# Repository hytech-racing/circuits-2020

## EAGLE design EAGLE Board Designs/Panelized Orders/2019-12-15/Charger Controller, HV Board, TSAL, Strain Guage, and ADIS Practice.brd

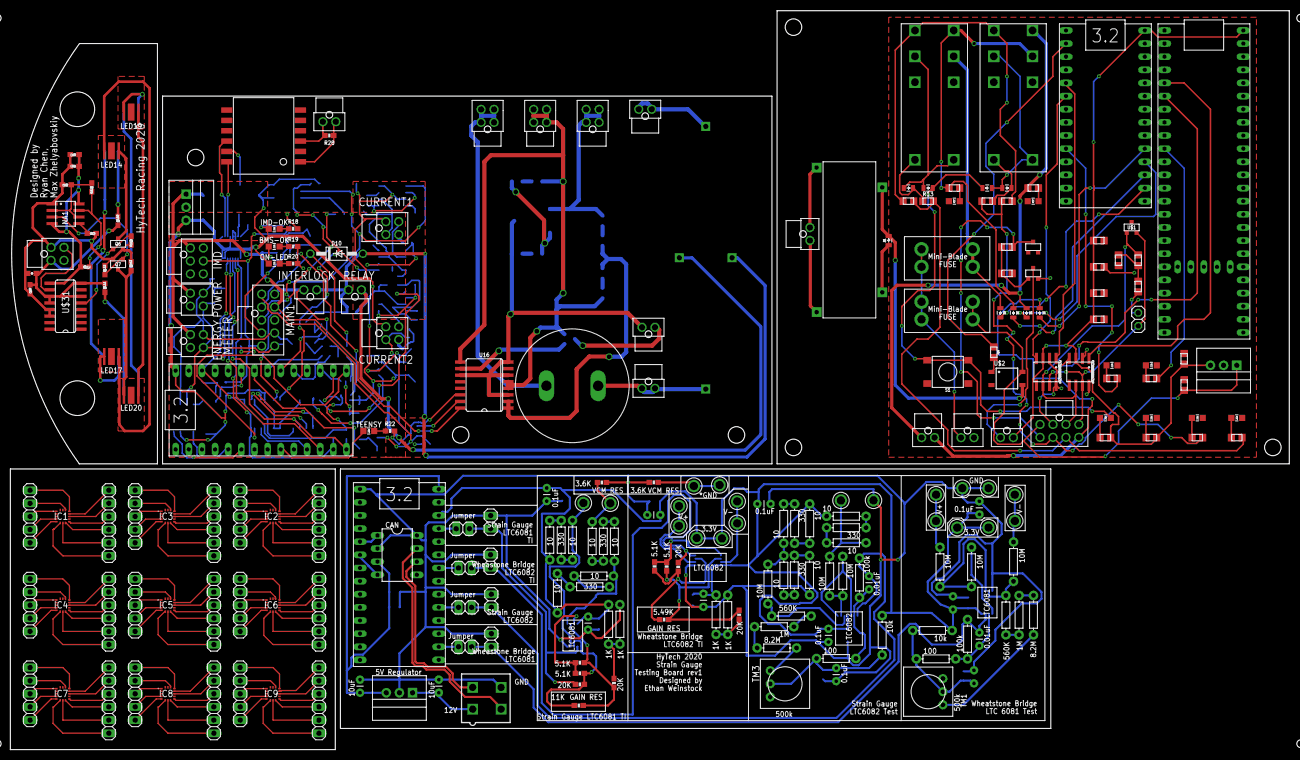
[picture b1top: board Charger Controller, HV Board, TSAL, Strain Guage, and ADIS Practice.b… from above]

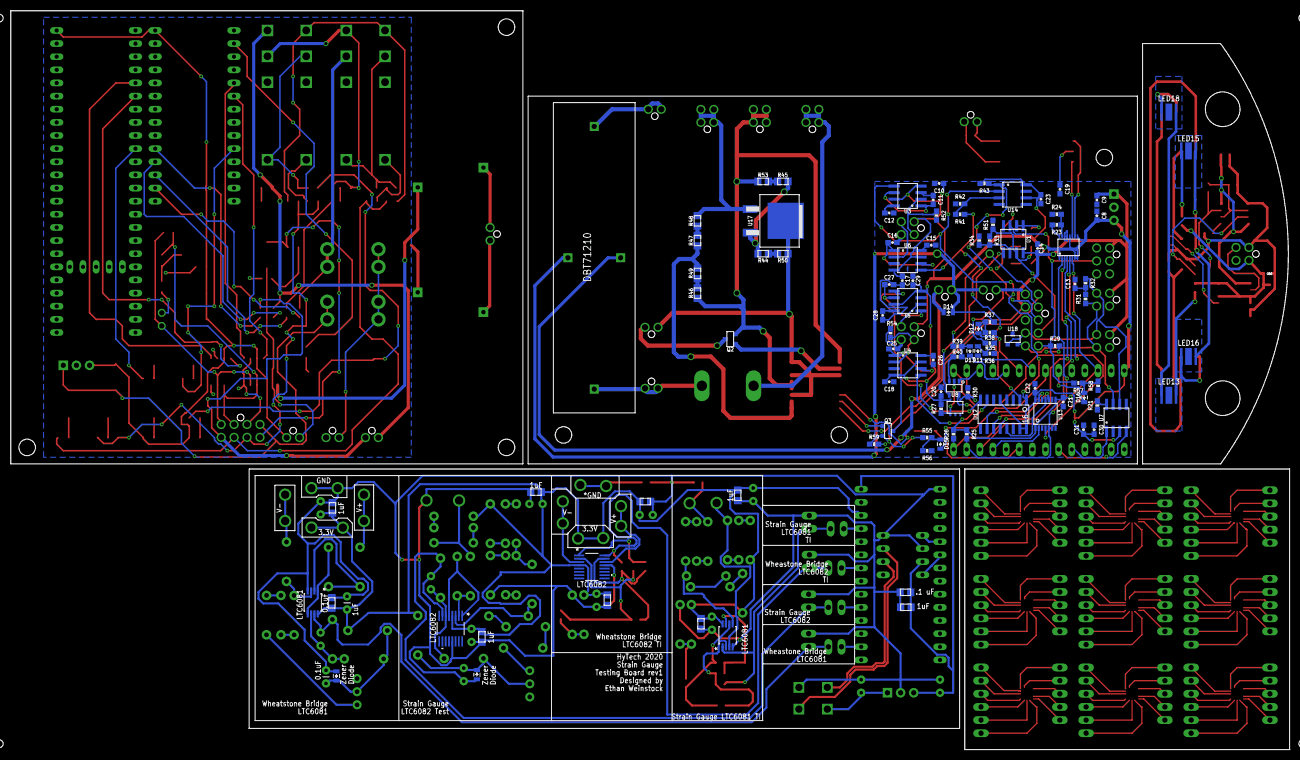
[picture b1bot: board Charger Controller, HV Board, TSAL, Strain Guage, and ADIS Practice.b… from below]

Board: 2 copper layers, 247.3 x 142.9 mm, 344 parts (105 on the bottom side), 312 nets.

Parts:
5ABOARDFUSE, 5ASHUTDOWNFUSE: MINI-BLADE_FUSE_HOLDER
BMS-OK: GREEN; LED-805
BMS_SHUTDOWN_RLY: RT424009; RELAY_DPDT
C1, C6, C40, C43, C47, C49, C55, C57, C59, C60: 1uF; 0805
C2, C7: .1uF; 0805
C3, C4: 10uF; 0805
C5: 4.7nF; 0805
C8, C9: 10uF; 0603-CAP
C10, C11, C14, C16, C17, C18, C20, C21, C22, C23, C25, C27, C29, C30, C31, C64, C67: 0.1uF; 0603-CAP
C12, C15, C26, C28: 530pF; 0603-CAP
C13: 4.7nF; 0603-CAP
C19: 27pF; 0603-CAP
C24: 180µF; LLS2V221MELZ
C38: 0.1uF; 0805
C39, C42, C44, C46, C48, C50, C56, C58, C61: 0.1uF; CAP-PTH-SMALL
C41, C45: 0.01uF; CAP-PTH-SMALL
C51: 1uF; CAP-PTH-SMALL
C52, C53: 10uF; CAP-PTH-SMALL
C54: .1 uF; 0805
C62: 4.7uF; 0603-CAP
C63: 10nF; 0603-CAP
C65, C66: 1uF; 0603-CAP
CAN_TERM_JMP: M02_SLIM; 1X02_SLIM
CAN_TRANSCEIVER_3.2, CAN_TRANSCEIVER_3.5: MCP2551; SOIC-08
CHARGER: CHARGE CONTROL; NANO-FIT_VERTICAL-2
CURRENT1, CURRENT2: CURRENT; NANO-FIT_VERTICAL-4
D1, D2, D4, D5, D6, D7, D8, D9, D11, D12, D13, D14, D15, D16: TS4148 RYG; 0805_D
D3: DIODE; 0805_D
D10: DIODE; DO-41
DISCH+: DISCHARGE+; NANO-FIT_VERTICAL-2
ENERGYMETER: ENERGY METER; NANO-FIT_VERTICAL-4
HV+FUSED_1A-IMD+: HV+; NANO-FIT_VERTICAL-4
HV+UNFUSED: HV+UNFUSED; NANO-FIT_VERTICAL-2
HV-FUSED_1A-IMD-: HV-; NANO-FIT_VERTICAL-4
HV-UNFUSED_DISCHARGE-: HV-UNFUSED; NANO-FIT_VERTICAL-4
IC1, IC2, IC3, IC4, IC5, IC6, IC7, IC8, IC9: KX124-1051; 3X3LGA
IMD: IMD; NANO-FIT_VERTICAL-6
IMD-OK: YELLOW; LED-805
IMD_SHUTDOWN_RLY: RT424009; RELAY_DPDT
INDICATOR: INDICATOR; NANO-FIT_VERTICAL-2
INTERLOCK: INTERLOCK; NANO-FIT_VERTICAL-2
ISO_SPI: ISO_SPI; NANO-FIT_VERTICAL-2
J1, J2, J3, J4: JUMPER.1; 1X02
JP1, JP2, JP5, JP7, JP9, JP11, JP13, JP15, JP17: 1X06
JP3, JP4, JP6, JP8, JP10, JP12, JP14, JP16, JP18: 1X05
JP19, JP20, JP21, JP22: M02; 1X02
LED1: Purple; LED-805
LED3: Yellow; LED-805
LED4: Green; LED-805
LED6: White; LED-805
LED13, LED18, LED19, LED20: RED; XP-E2
LED14, LED15, LED16, LED17: GRN; XP-E2
LT1790B, LT1790B2: 1.25V; 0805_D
MAIN: MAIN CONNECTOR; NANO-FIT_VERTICAL-8
MAIN1: MAIN; NANO-FIT_VERTICAL-10
NA1: NA555SO-8; SOIC-08
ON-LED: PURPLE; LED-805
POWER: POWER; NANO-FIT_VERTICAL-2
POWER1: POWER; NANO-FIT_VERTICAL-4
POWERTAIL: Powerswitch Tail; NANO-FIT_VERTICAL-2
Q1, Q6, Q7: SOT23
Q2, Q3: DMG3406L; SOT23
R1, R13: 20; 0805
R1_1, R1_3, R1_6, R1_8: 5.1K; 0603-RES
R1_2, R1_4, R1_5, R1_7: 20K; 0603-RES
R1_9: 5.49K; 0603-RES
R1_11: 11K; 0603-RES
R2, R3, R7, R16, R44, R50: 2k; 0805
R4, R45, R53: 20k; 0805
R5: 270; 0805
R6: 5.1k; 0805
R8: 33; 0805
R9, R10: 60; 0805
R11: 40k; 0805
R12: 10k; 0805
R14: 360; 0805
R15, R17: 68; 0805
R18: 820; 0603-RES
R19, R25, R26, R29, R34, R43, R51, R59, R113, R114, R115: 2k; 0603-RES
R20: 270; 0603-RES
R21, R23, R24, R112: 1k; 0603-RES
R22: 43; 0603-RES
R27: 430; 0603-RES
R28: 100; 0603-RES
R30: 10k; 0603-RES
R31, R32: 60; 0603-RES
R33: 4k; 0603-RES
R35, R37, R39, R57: 43k; 0603-RES
R36, R38, R40, R58: 12k; 0603-RES
R41: 261; 0603-RES
R42: 5K; 0603-RES
R46: 1.4k; 0805
R47, R48: 510k; 0805
R49: 14k; 0805
R52, R54: 10K; 0603-RES
R55, R56: 5k; 0603-RES
R67, R70, R71, R72, R74, R85: 10M; AXIAL-0.3
R68, R69, R78, R80, R82, R83, R87, R89, R99, R100, R102, R103: 10; AXIAL-0.3
R73, R81: 8.2M; AXIAL-0.3
R75, R91: 100k; AXIAL-0.3
R76, R95: 100; AXIAL-0.3
R77, R96: 10k; AXIAL-0.3
R79, R84, R86, R88, R98, R104: 330; AXIAL-0.3
R90, R93: 1M; AXIAL-0.3
R92, R94: 560K; AXIAL-0.3
R97, R108: 3.6K; 0603-RES
R101, R105, R106, R107: 1K; AXIAL-0.3
R109, R111: 330R; 0603-RES
R110: 50k; 0603-RES
REG, REG1: 5V; OKI-78SR
RELAY: RELAY; NANO-FIT_VERTICAL-2
S1: TACTILE_SWITCH_SMD_6.2MM_TALL
SHUTDOWN_B: Yellow; LED-805
SHUTDOWN_BUTTON: Shutdown Button; NANO-FIT_VERTICAL-2
SHUTDOWN_C: Green; LED-805
STATUS, STATUS1: RED; LED-805
TEENSY: BLUE; LED-805
TEENSY3.2: TEENSY_3.2_SIMPLE
TM1, TM3: 500k; TRIM-3386
U1: OPA2172; SOIC-08
U2: OKI-78SR-5; OKI-78SR
U3, U4, U5, U6: MAX7480; SOIC-08
U7: MCP2551; SOIC-08
U8: SN74LVC1G08; SOT-23-5
U9: LTC6820; MSOP-16
U10: STWD100; SOT23-5
U11: HM2102NLT
U12: MCP3208SOIC; SOIC-16
U13: TXB0104TSSOP; TSSOP-14
U14: MCP6542SOIC; SOIC-08
U15: DBT71210
U16: UCC21520A; SO16-DW
U17: LR8; TO-252
U18: CDSOT23-T24CAN-Q; SOT23
U19, U20: LTC6082CGNPBF; SSOP-16_GN
U$1: CDSOT23-T24CAN-Q; SOT23
U$2: CPC1002N; SOP04
U$3: KT12-1A-40L-THT
U$4, U$8: TEENSY_3.2_SIMPLE
U$5: TEENSY_3.5_EXT
U$7, U$21: LTC6081; MSOP-8_MS
U$9, U$10, U$11, U$12, U$13, U$14, U$15, U$16, U$17, U$18, U$19, U$20, U$23, U$24, U$25, U$26, U$27, U$28, U$29, U$30: TEST_POINT
U$22: MCP2551DIL; DIL08
U$31: MAX4622; SO16
X2: CONNECTOR-4; MINIFIT_5566-4
X3: CONNECTOR-4NANO-FIT-VERTICAL-4; NANO-FIT_VERTICAL-4
ZENER: SOT23

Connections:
3V3: C38.2, C39.1, C40.1, C42.2, C43.1, C46.1, C47.1, C48.1, C49.1, C51.1, C56.2, C57.1, C58.1, C59.1, C60.1, C61.2, R77.P$2, R78.P$1, R80.P$1, R96.P$2, R99.P$2, R101.P$2, R103.P$2, R106.P$2, U19.4, U20.4, U$7.8, U$8.3.3V, U$11.P$1, U$18.P$1, U$21.8, U$23.P$1, U$30.P$1
60V_THRESHOLD_SIGNAL: MAIN1.P$1, Q3.2, R55.1, R59.1
60V_THRESHOLD_TEENSY: D15.C, TEENSY3.2.A6
+3V3: C21.1, R25.1, R26.1, TEENSY3.2.3.3V, U8.5, U9.6, U13.1, U13.8
+5V: C1.2, C2.2, C4.2, C6.2, C7.2, CAN_TRANSCEIVER_3.2.3, CAN_TRANSCEIVER_3.5.3, POWERTAIL.P$1, R5.1, R6.1, REG.3, U$4.VIN, U$5.VIN
+5V1: C8.1, C10.1, C17.1, C18.1, C20.1, C22.1, C23.1, C29.1, C30.1, C31.1, CURRENT1.P$1, CURRENT2.P$1, ON-LED.A, Q3.3, R27.1, R43.2, TEENSY3.2.VIN, U2.3, U3.4, U3.7, U4.4, U4.7, U5.4, U5.7, U6.4, U6.7, U7.3, U9.1, U9.7, U9.8, U9.9, U9.12, U10.VCC, U12.5, U12.15, U12.16, U13.14, U14.6, U14.8
+5V2: C53.2, C54.2, C55.2, REG1.3, U$8.VIN, U$22.3
+12V: 5ABOARDFUSE.R1, 5ABOARDFUSE.R2, C3.2, MAIN.P$4, REG.1, U$2.4
+12V1: C9.1, C14.1, ENERGYMETER.P$1, IMD.P$1, MAIN1.P$7, POWER1.P$1, U1.8, U2.1, U16.16
+12V2: C52.2, REG1.1, X2.1
+12VIN: 5ABOARDFUSE.L1, 5ABOARDFUSE.L2, 5ASHUTDOWNFUSE.L1, 5ASHUTDOWNFUSE.L2, POWER.P$2
BMS_OK: MAIN.P$7, R1.1, R2.1, R8.1
BMS_OK_3.3V: U1.5, U8.4
BMS_OK_10V: BMS-OK.A, MAIN1.P$4, R33.2, R51.1, U1.7
BMS_OK_RELAY: BMS_SHUTDOWN_RLY.COIL+, D6.C, R1.2
BMS_PWR_STEP: BMS_SHUTDOWN_RLY.3, BMS_SHUTDOWN_RLY.COIL-, D1.A, D6.A
BSPD_CURR_REFERENCE: R41.1, R42.2, U14.3
BSPD_CURR_SIGNAL: MAIN1.P$3, R43.1, U14.1
CANH: CAN_TERM_JMP.1, CAN_TRANSCEIVER_3.2.7, CAN_TRANSCEIVER_3.5.7, MAIN.P$1, U$1.2
CANH1: ENERGYMETER.P$4, MAIN1.P$10, POWER1.P$4, R31.2, U7.7, U18.2
CANH2: U$22.7, X2.3
CANL: CAN_TRANSCEIVER_3.2.6, CAN_TRANSCEIVER_3.5.6, MAIN.P$2, R9.1, U$1.1
CANL1: ENERGYMETER.P$3, MAIN1.P$9, POWER1.P$3, R32.2, U7.6, U18.1
CANL2: U$22.6, X2.2
CHARGER_1: CHARGER.P$1, U$3.S1
CHARGER_2: CHARGER.P$2, U$3.S2
CHARGE_CONTROL: D3.C, U$2.3, U$3.C1
CHARGE_ENABLE: MAIN.P$8, R11.2, ZENER.3
CHARGE_ENABLE1: D10.C, MAIN1.P$2, R39.1
CHARGE_ENABLE_TEENSY: D13.C, TEENSY3.2.A3
CS_LTC6820: TEENSY3.2.D10(TX2), U9.5
CS_MCP3208_3.3V: TEENSY3.2.D9(RX2), U13.2
CURR1_SENSE: CURRENT1.P$2, R52.1, U3.2
CURR1_SENSE_FILTERED: U3.5, U12.1, U14.2
CURR2_SENSE: CURRENT2.P$2, R54.1, U4.2
CURR2_SENSE_FILTERED: U4.5, U12.7
DISCHARGE_RELAY_GND: D14.A, RELAY.P$2, U15.COIL-
GND: C1.1, C2.1, C3.1, C4.1, C5.2, C6.1, C7.1, CAN_TRANSCEIVER_3.2.2, CAN_TRANSCEIVER_3.2.8, CAN_TRANSCEIVER_3.5.2, CAN_TRANSCEIVER_3.5.8, D3.A, LED1.C, LED3.C, LED4.C, MAIN.P$3, POWER.P$1, Q1.2, R12.1, REG.2, S1.B1, S1.B2, SHUTDOWN_B.C, SHUTDOWN_C.C, STATUS.C, STATUS1.C, U$1.3, U$2.2, U$3.C2, U$4.GND, U$5.GND, ZENER.1
GND1: C8.2, C9.2, C10.2, C11.2, C12.2, C13.1, C14.2, C15.2, C16.2, C17.2, C18.2, C19.2, C20.2, C21.2, C22.2, C23.2, C25.2, C26.2, C27.2, C28.2, C29.2, C30.2, C31.2, CURRENT1.P$4, CURRENT2.P$4, ENERGYMETER.P$2, IMD.P$2, IMD.P$3, IMD.P$4, MAIN1.P$8, POWER1.P$2, R18.1, R19.2, R20.2, R21.1, R22.2, R24.2, R29.2, R30.2, R34.1, R36.1, R38.1, R40.1, R42.1, R51.2, R52.2, R54.2, R56.1, R58.1, R59.2, TEENSY3.2.AGND, TEENSY3.2.GND, U1.4, U2.2, U3.3, U4.3, U5.3, U6.3, U7.2, U8.3, U9.13, U9.14, U10.EN, U10.GND, U12.4, U12.9, U12.14, U13.7, U14.4, U14.5, U16.14, U18.3
GND1_A: IC1.5, JP10.1
GND1_B: IC2.5, JP12.1
GND1_C: IC3.5, JP6.1
GND1_D: IC4.5, JP4.1
GND1_E: IC5.5, JP8.1
GND1_F: IC6.5, JP3.1
GND1_G: IC7.5, JP14.1
GND1_H: IC8.5, JP16.1
GND1_I: IC9.5, JP18.1
GND2_A: IC1.12, JP9.6
GND2_B: IC2.12, JP11.6
GND2_C: IC3.12, JP5.6
GND2_D: IC4.12, JP1.6
GND2_E: IC5.12, JP7.6
GND2_F: IC6.12, JP2.6
GND2_G: IC7.12, JP13.6
GND2_H: IC8.12, JP15.6
GND2_I: IC9.12, JP17.6
GND3: C38.1, C39.2, C40.2, C42.1, C43.2, C44.1, C46.2, C47.2, C48.2, C49.2, C50.1, C51.2, C52.1, C53.1, C54.1, C55.1, C56.1, C57.2, C58.2, C59.2, C60.2, C61.1, JP19.1, JP20.1, JP21.1, JP22.1, LT1790B.A, LT1790B2.A, R89.P$1, R97.1, R105.P$1, R107.P$1, R108.1, REG1.2, U19.13, U20.13, U$7.4, U$8.GND, U$14.P$1, U$15.P$1, U$20.P$1, U$21.4, U$22.2, U$22.8, X2.4
GND4: C62.2, C63.2, C64.2, C65.2, C66.2, C67.2, NA1.1, Q6.2, Q7.2, R113.2, R114.2, R115.2, U$31.13, U$31.14, X3.P$1
GRN1: Q6.1, R114.1, U$31.5
HV+FUSED_1A: HV+FUSED_1A-IMD+.P$1, HV+FUSED_1A-IMD+.P$2, HV+FUSED_1A-IMD+.P$3, HV+FUSED_1A-IMD+.P$4, R48.2, U17.1
HV+UNFUSED: C24.P$1, HV+UNFUSED.P$1, HV+UNFUSED.P$2, U15.CONTACT1
HV+UNFUSED_FSAE_DISCHARGE: DISCH+.P$1, DISCH+.P$2, U15.CONTACT2
HV-FUSED_1A: HV-FUSED_1A-IMD-.P$1, HV-FUSED_1A-IMD-.P$2, HV-FUSED_1A-IMD-.P$3, HV-FUSED_1A-IMD-.P$4, Q2.2, R46.1, R53.2, U16.4, U16.5, U16.9
HV-UNFUSED: C24.P$2, HV-UNFUSED_DISCHARGE-.P$1, HV-UNFUSED_DISCHARGE-.P$2, HV-UNFUSED_DISCHARGE-.P$3, HV-UNFUSED_DISCHARGE-.P$4
IM: U9.10, U11.P$10
IMD_PWR_STEP: D7.A, D9.A, IMD_SHUTDOWN_RLY.3, IMD_SHUTDOWN_RLY.COIL-
INB-: C45.1, R91.P$1, R95.P$2, U$7.6
INT1_A: IC1.11, JP9.5
INT1_B: IC2.11, JP11.5
INT1_C: IC3.11, JP5.5
INT1_D: IC4.11, JP1.5
INT1_E: IC5.11, JP7.5
INT1_F: IC6.11, JP2.5
INT1_G: IC7.11, JP13.5
INT1_H: IC8.11, JP15.5
INT1_I: IC9.11, JP17.5
INT2_A: IC1.9, JP9.4
INT2_B: IC2.9, JP11.4
INT2_C: IC3.9, JP5.4
INT2_D: IC4.9, JP1.4
INT2_E: IC5.9, JP7.4
INT2_F: IC6.9, JP2.4
INT2_G: IC7.9, JP13.4
INT2_H: IC8.9, JP15.4
INT2_I: IC9.9, JP17.4
IO_VDD_A: IC1.1, JP10.3
IO_VDD_B: IC2.1, JP12.3
IO_VDD_C: IC3.1, JP6.3
IO_VDD_D: IC4.1, JP4.3
IO_VDD_E: IC5.1, JP8.3
IO_VDD_F: IC6.1, JP3.3
IO_VDD_G: IC7.1, JP14.3
IO_VDD_H: IC8.1, JP16.3
IO_VDD_I: IC9.1, JP18.3
IP: U9.11, U11.P$12
ISOSPI-M: ISO_SPI.P$2, R28.2, U11.P$3
ISOSPI-P: ISO_SPI.P$1, R28.1, U11.P$1
LATCH_EXT_BUTTON: D1.C, D9.C, LED6.C, S1.A1, S1.A2
MISO: R26.2, TEENSY3.2.D12, U9.3, U12.12
MOSI_5V: U12.11, U13.10
MOSI_TEENSY: R25.2, TEENSY3.2.D11, U9.2, U13.5
unnamed: POWERTAIL.P$2, Q1.3
unnamed: LED6.A, R6.2
unnamed: LED4.A, R8.2
unnamed: CAN_TRANSCEIVER_3.5.4, U$5.D4(CANRX)
unnamed: Q1.1, R11.1, R12.2
unnamed: CAN_TRANSCEIVER_3.5.1, U$5.D3(CANTX)
unnamed: R17.1, STATUS1.A
unnamed: R15.1, STATUS.A
unnamed: R17.2, U$5.D8(TX3)
unnamed: R14.2, U$2.1
unnamed: R15.2, U$4.D8(TX3)
unnamed: D7.C, IMD_SHUTDOWN_RLY.COIL+, R13.2
unnamed: ON-LED.C, R20.1
unnamed: R21.2, U7.8
unnamed: CAN_TRANSCEIVER_3.2.4, U$4.D4(CANRX)
unnamed: R22.1, TEENSY.C
unnamed: CAN_TERM_JMP.2, R10.2
unnamed: R23.2, R24.1, U9.15
unnamed: R3.2, SHUTDOWN_B.A
unnamed: C11.1, U3.1, U3.6
unnamed: C12.1, U3.8
unnamed: CAN_TRANSCEIVER_3.2.1, U$4.D3(CANTX)
unnamed: U12.10, U13.13
unnamed: C13.2, R31.1, R32.1
unnamed: TEENSY3.2.D3(CANTX), U7.1
unnamed: LED3.A, R7.2
unnamed: R33.1, R34.2, U1.6
unnamed: D11.A, R35.2, R36.2
unnamed: LED1.A, R5.2
unnamed: D12.A, R37.2, R38.2
unnamed: R23.1, U9.16
unnamed: R4.2, SHUTDOWN_C.A
unnamed: D13.A, R39.2, R40.2
unnamed: R44.1, R45.1, U17.3
unnamed: C19.1, U11.P$11
unnamed: TEENSY3.2.D4(CANRX), U7.4
unnamed: TEENSY.A, TEENSY3.2.D7(RX3)
unnamed: R27.2, U8.2, U10.WDO
unnamed: R47.1, R48.1
unnamed: TEENSY3.2.A1, U8.1
unnamed: R47.2, R49.2, U16.1, U16.2
unnamed: IMD-OK.A, U1.1, U1.2
unnamed: R46.2, R49.1
unnamed: BMS-OK.C, R19.1
unnamed: IMD-OK.C, R18.2
unnamed: R44.2, R50.1
unnamed: R45.2, R53.1
unnamed: C16.1, U6.1, U6.6
unnamed: C15.1, U6.8
unnamed: R30.1, TEENSY3.2.A0, U10.WDI
unnamed: C25.1, U4.1, U4.6
unnamed: C26.1, U4.8
unnamed: C27.1, U5.1, U5.6
unnamed: C28.1, U5.8
unnamed: INDICATOR.P$2, Q2.3
unnamed: Q3.1, U16.15
unnamed: Q2.1, U16.10
unnamed: INDICATOR.P$1, R50.2, U16.3, U16.6, U16.8, U16.11, U17.2(TAB)
unnamed: D15.A, R55.2, R56.2
unnamed: BMS_SHUTDOWN_RLY.4, IMD_SHUTDOWN_RLY.4, R2.2, R16.2
unnamed: D16.A, R57.2, R58.2
unnamed: C5.1, R9.2, R10.1
unnamed: R67.P$2, R85.P$2, U$7.2
unnamed: R72.P$2, R94.P$1, U$7.3
unnamed: C50.2, LT1790B.C, R95.P$1, R96.P$1, TM1.2
unnamed: R81.P$2, TM1.1
unnamed: J1.1, U$8.A0
unnamed: J2.1, U$8.A3
unnamed: J3.1, U$8.A6
unnamed: R68.P$2, R69.P$2, R71.P$1
unnamed: C44.2, LT1790B2.C, R76.P$1, R77.P$1, TM3.2
unnamed: R73.P$2, TM3.1
unnamed: R79.P$2, R83.P$1
unnamed: R69.P$1, R84.P$2
unnamed: R82.P$1, R86.P$2
unnamed: R78.P$2, R86.P$1
unnamed: R79.P$1, R87.P$2
unnamed: R68.P$1, R88.P$2
unnamed: R80.P$2, R88.P$1
unnamed: R84.P$1, R89.P$2
unnamed: R73.P$1, R90.P$1
unnamed: R90.P$2, R92.P$2
unnamed: R81.P$1, R93.P$1
unnamed: R93.P$2, R94.P$2
unnamed: U$8.D3(CANTX), U$22.1
unnamed: U$8.D4(CANRX), U$22.4
unnamed: R98.P$1, R100.P$2
unnamed: R98.P$2, R99.P$1
unnamed: R1_3.1, R1_4.2, R1_11.1, U$21.6
unnamed: R1_1.2, R1_3.2, U$21.7
unnamed: R1_1.1, R1_2.1, R1_11.2, U$21.2
unnamed: R1_4.1, R101.P$1, R105.P$2
unnamed: R102.P$2, R104.P$1
unnamed: R103.P$1, R104.P$2
unnamed: R1_5.1, R106.P$1, R107.P$2
unnamed: J4.1, U$8.A9
unnamed: R108.2, U$26.P$1, U$27.P$1
unnamed: LED14.C, Q6.3
unnamed: C62.1, NA1.2, NA1.6, R110.1
unnamed: NA1.7, R110.2, R112.2
unnamed: LED13.A, R111.1
unnamed: LED20.C, Q7.3, R113.1
unnamed: C63.1, NA1.5
unnamed: LED15.A, R109.2
unnamed: LED14.A, LED17.C
unnamed: LED13.C, LED18.A
unnamed: LED18.C, LED19.A
unnamed: LED19.C, LED20.A
unnamed: LED16.C, LED17.A
unnamed: LED15.C, LED16.A
NCS_A: IC1.8, JP9.3
NCS_B: IC2.8, JP11.3
NCS_C: IC3.8, JP5.3
NCS_D: IC4.8, JP1.3
NCS_E: IC5.8, JP7.3
NCS_F: IC6.8, JP2.3
NCS_G: IC7.8, JP13.3
NCS_H: IC8.8, JP15.3
NCS_I: IC9.8, JP17.3
OKHS: MAIN.P$6, R7.1, R13.1, R16.1
OKHS1: IMD.P$5, MAIN1.P$5, R29.1, R57.1, U1.3
OKHS_TEENSY: D16.C, TEENSY3.2.A7
OUT1: R85.P$1, U$7.1, U$7.5
OUT4: R74.P$1, U19.1, U19.5
OUT4A+: R71.P$2, R92.P$1, U19.3
OUT4A-: R70.P$2, R74.P$2, U19.2
RED1: NA1.3, Q7.1, R115.1
REF1_SENSE: CURRENT1.P$3, U6.2
REF1_SENSE_FILTERED: R41.2, U6.5, U12.2
REF2_SENSE: CURRENT2.P$3, U5.2
REF2_SENSE_FILTERED: U5.5, U12.8
SCK_5V: U12.13, U13.11
SCK_TEENSY: TEENSY3.2.D13, U9.4, U13.4
SCLK_A: IC1.4, JP10.2
SCLK_B: IC2.4, JP12.2
SCLK_C: IC3.4, JP6.2
SCLK_D: IC4.4, JP4.2
SCLK_E: IC5.4, JP8.2
SCLK_F: IC6.4, JP3.2
SCLK_G: IC7.4, JP14.2
SCLK_H: IC8.4, JP16.2
SCLK_I: IC9.4, JP18.2
SDI_A: IC1.6, JP9.1
SDI_B: IC2.6, JP11.1
SDI_C: IC3.6, JP5.1
SDI_D: IC4.6, JP1.1
SDI_E: IC5.6, JP7.1
SDI_F: IC6.6, JP2.1
SDI_G: IC7.6, JP13.1
SDI_H: IC8.6, JP15.1
SDI_I: IC9.6, JP17.1
SDO_A: IC1.7, JP9.2
SDO_B: IC2.7, JP11.2
SDO_C: IC3.7, JP5.2
SDO_D: IC4.7, JP1.2
SDO_E: IC5.7, JP7.2
SDO_F: IC6.7, JP2.2
SDO_G: IC7.7, JP13.2
SDO_H: IC8.7, JP15.2
SDO_I: IC9.7, JP17.2
SG_BOT: R87.P$1, R97.2, U$19.P$1
SG_V1: R82.P$2, R83.P$2, U$21.5
SG_V2: R100.P$1, U$9.P$1, U$21.3
SHUTDOWN_A: 5ASHUTDOWNFUSE.R1, 5ASHUTDOWNFUSE.R2, D8.A, IMD_SHUTDOWN_RLY.6
SHUTDOWN_A_TEENSY: D8.C, U$4.A0
SHUTDOWN_B: BMS_SHUTDOWN_RLY.6, D5.A, IMD_SHUTDOWN_RLY.5, R3.1
SHUTDOWN_B_TEENSY: D5.C, U$4.A1
SHUTDOWN_C: BMS_SHUTDOWN_RLY.5, D4.A, R4.1, SHUTDOWN_BUTTON.P$2
SHUTDOWN_C_TEENSY: D4.C, U$4.A2
SHUTDOWN_D: D2.A, MAIN.P$5, SHUTDOWN_BUTTON.P$1
SHUTDOWN_D_TEENSY: D2.C, U$4.A3
SHUTDOWN_G: INTERLOCK.P$1, MAIN1.P$6, R35.1
SHUTDOWN_G_TEENSY: D11.C, TEENSY3.2.A5
SHUTDOWN_H: D10.A, D14.C, INTERLOCK.P$2, R37.1, RELAY.P$1, U15.COIL+
SHUTDOWN_H_TEENSY: D12.C, TEENSY3.2.A4
SIGNAL1: U$31.10, X3.P$3
TOGGLE_CHARGER: R14.1, U$4.D0(RX1)
TRIG_A: IC1.13, JP10.5
TRIG_B: IC2.13, JP12.5
TRIG_C: IC3.13, JP6.5
TRIG_D: IC4.13, JP4.5
TRIG_E: IC5.13, JP8.5
TRIG_F: IC6.13, JP3.5
TRIG_G: IC7.13, JP14.5
TRIG_H: IC8.13, JP16.5
TRIG_I: IC9.13, JP18.5
V1: C64.1, C65.1, NA1.4, NA1.8, R112.1, U$31.9
V+1: R67.P$1, U$12.P$1, U$13.P$1
V-1: R72.P$1, U$16.P$1, U$17.P$1
VCC1: C66.1, C67.1, R109.1, R111.2, U$31.6, U$31.8, U$31.11, U$31.12, X3.P$2
VDD_A: IC1.14, JP10.4
VDD_B: IC2.14, JP12.4
VDD_C: IC3.14, JP6.4
VDD_D: IC4.14, JP4.4
VDD_E: IC5.14, JP8.4
VDD_F: IC6.14, JP3.4
VDD_G: IC7.14, JP14.4
VDD_H: IC8.14, JP16.4
VDD_I: IC9.14, JP18.4
VOUT1: C45.2, J1.2, JP19.2, R91.P$2, U$7.7
VOUT2: J3.2, JP22.2, R1_7.2, U20.16
VOUT3: J4.2, JP21.2, R1_2.2, U$21.1
VOUT4: C41.2, J2.2, JP20.2, R75.P$2, U19.7
VOUT4-: C41.1, R75.P$1, R76.P$2, U19.6
VR4-2: R70.P$1, R102.P$1, U$10.P$1
VREF: R1_5.2, R1_8.1, R1_9.1, U20.2
WBV1: U20.3, U$28.P$1, U$29.P$1
WBV1OUT: R1_6.2, R1_8.2, U20.1
WBV2: U20.14, U$24.P$1, U$25.P$1
WBV2-I: R1_6.1, R1_7.1, R1_9.2, U20.15

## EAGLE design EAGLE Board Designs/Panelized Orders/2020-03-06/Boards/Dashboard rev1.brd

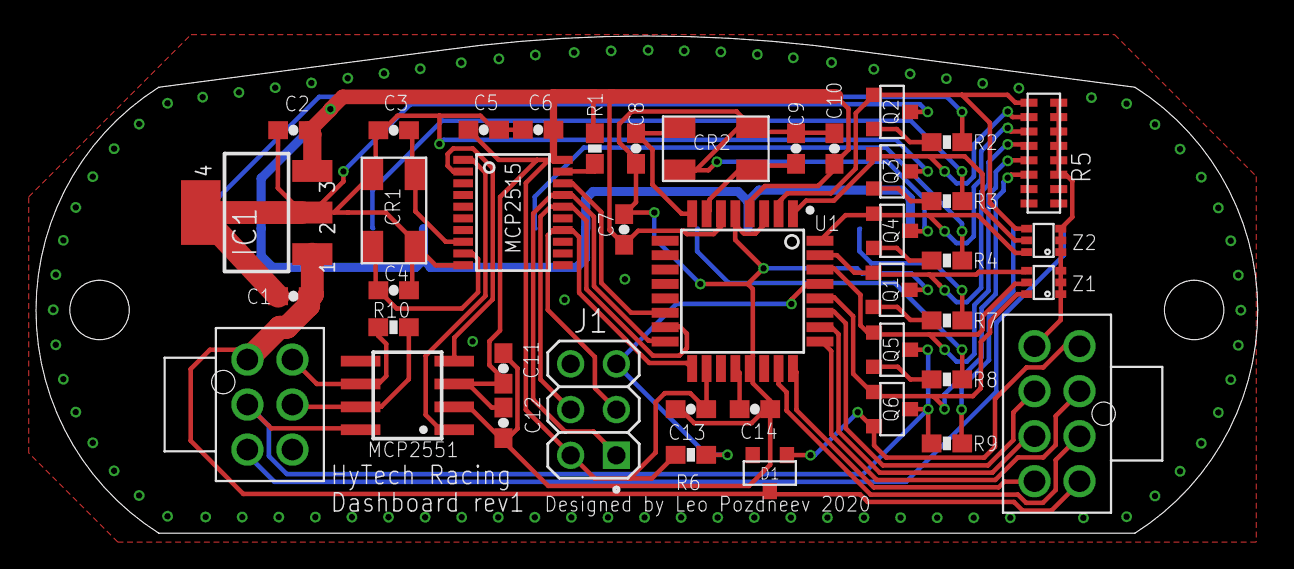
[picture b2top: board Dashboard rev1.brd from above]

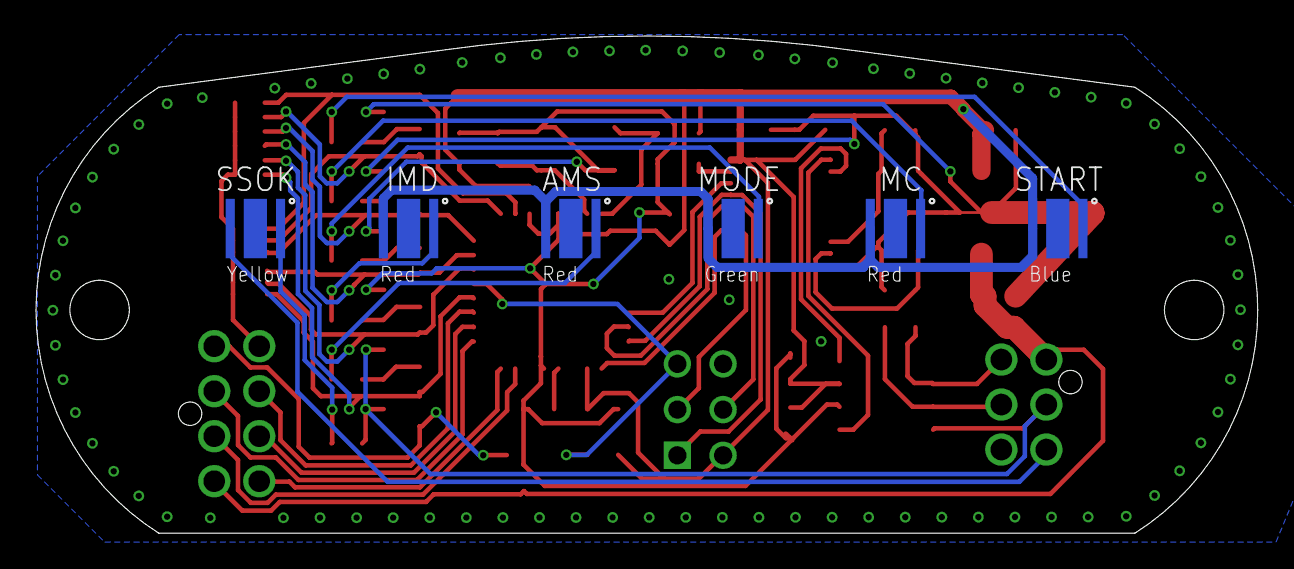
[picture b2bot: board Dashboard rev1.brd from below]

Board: 2 copper layers, 67.9 x 27.6 mm, 48 parts (6 on the bottom side), 42 nets.

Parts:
$$X2: CONNECTOR-8NANO-FIT_VERTICAL-8; NANO-FIT_VERTICAL-8
AMS: Red; CREE_XP-E2
C1: 0.22uF; 0603-CAP
C2, C6, C7, C10, C12, C13: 0.1uF; 0603-CAP
C3, C4, C8, C9: 14pF; 0603-CAP
C5, C11: 1uF; 0603-CAP
C14: .1uF; 0603-CAP
CR1, CR2: 16MHz, 10pF; ABM3B
D1: DIODE_ZENER; SOT23
IC1: LM340S; SOT223
IMD: Red; CREE_XP-E2
J1: AVR-ISP-HEADER; 2X03
MC: Red; CREE_XP-E2
MCP2515: MCP2515TSSOP; TSSOP-20
MCP2551: MCP2551; SOIC-08
MODE: Green; CREE_XP-E2
Q1, Q2, Q3, Q4, Q5, Q6: SOT23
R1, R6: 10k; 0603-RES
R2, R3, R4, R7, R8, R9: 0603-RES
R5: 10k; CAT16-*8
R10: 120; 0603-RES
SSOK: Yellow; CREE_XP-E2
START: Blue; CREE_XP-E2
U1: ATMEGA328P-AU; QFP80P900X900X120-32N
X1: CONNECTOR-6NANO-FIT_VERTICAL-6; NANO-FIT_VERTICAL-6
Z1, Z2: MMBZ5245BTS-7-F; SOT363

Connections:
+5V: AMS.P$1, C2.1, C5.1, C6.1, C7.1, C10.1, C11.1, C12.1, C13.1, IC1.3, IMD.P$1, J1.2, MC.P$1, MCP2515.20, MCP2551.3, MODE.P$1, R1.2, R6.2, START.P$1, U1.4, U1.6, U1.18
+12V: $$X2.P$1, C1.2, D1.3, IC1.1, X1.P$1
BTN_EXTRA: $$X2.P$7, U1.27
BTN_MARK_READ: $$X2.P$2, U1.23
BTN_MC_CYCLE_READ: $$X2.P$3, U1.25
BTN_MODE_READ: $$X2.P$5, U1.24
BTN_START_READ: $$X2.P$6, U1.26
BUZZER_CTRL: Q6.1, R5.P$6, U1.28, Z1.P$4
BUZZER_OUT: $$X2.P$4, D1.1, Q6.2
CANH: MCP2551.7, R10.1, X1.P$5
CANL: MCP2551.6, R10.2, X1.P$4
CS: MCP2515.18, U1.14
GND: $$X2.P$8, C1.1, C2.2, C3.1, C4.2, C5.2, C6.2, C7.2, C8.2, C9.1, C10.2, C11.2, C12.2, C13.2, C14.2, CR1.P$2, CR1.P$4, CR2.P$2, CR2.P$4, IC1.2, IC1.4, J1.6, MCP2515.10, MCP2551.2, MCP2551.8, Q1.3, Q2.3, Q3.3, Q4.3, Q5.3, Q6.3, R5.P$11, R5.P$12, R5.P$13, R5.P$14, R5.P$15, R5.P$16, R9.2, U1.3, U1.5, U1.21, X1.P$2, Z1.P$1, Z1.P$2, Z1.P$3, Z2.P$1, Z2.P$2, Z2.P$3
LED_AMS_CTRL: Q5.1, R5.P$5, U1.30, Z1.P$5
LED_IMD_CTRL: Q1.1, R5.P$4, U1.31, Z1.P$6
LED_MC_ERR_CTRL: Q3.1, R5.P$2, U1.1, Z2.P$5
LED_MODE_CTRL: Q4.1, R5.P$3, U1.32, Z2.P$4
LED_START_CTRL: Q2.1, R5.P$1, U1.2, Z2.P$6
MISO: J1.1, MCP2515.17, U1.16
MOSI: J1.4, MCP2515.16, U1.15
unnamed: MCP2515.19, R1.1
unnamed: C4.1, CR1.P$3, MCP2515.9
unnamed: C3.2, CR1.P$1, MCP2515.8
unnamed: Q2.2, R2.2
unnamed: C9.2, CR2.P$1, U1.7
unnamed: C8.1, CR2.P$3, U1.8
unnamed: C14.1, U1.20
unnamed: Q4.2, R4.2
unnamed: MODE.P$2, R4.1
unnamed: R2.1, START.P$2
unnamed: Q1.2, R7.2
unnamed: IMD.P$2, R7.1
unnamed: R9.1, SSOK.P$2
unnamed: AMS.P$2, R8.1
unnamed: Q5.2, R8.2
unnamed: Q3.2, R3.2
unnamed: MC.P$2, R3.1
RESET: J1.5, R6.1, U1.29
RX: MCP2515.2, MCP2551.4
SCK: J1.3, MCP2515.14, U1.17
SSOK: SSOK.P$1, X1.P$3
TX: MCP2515.1, MCP2551.1

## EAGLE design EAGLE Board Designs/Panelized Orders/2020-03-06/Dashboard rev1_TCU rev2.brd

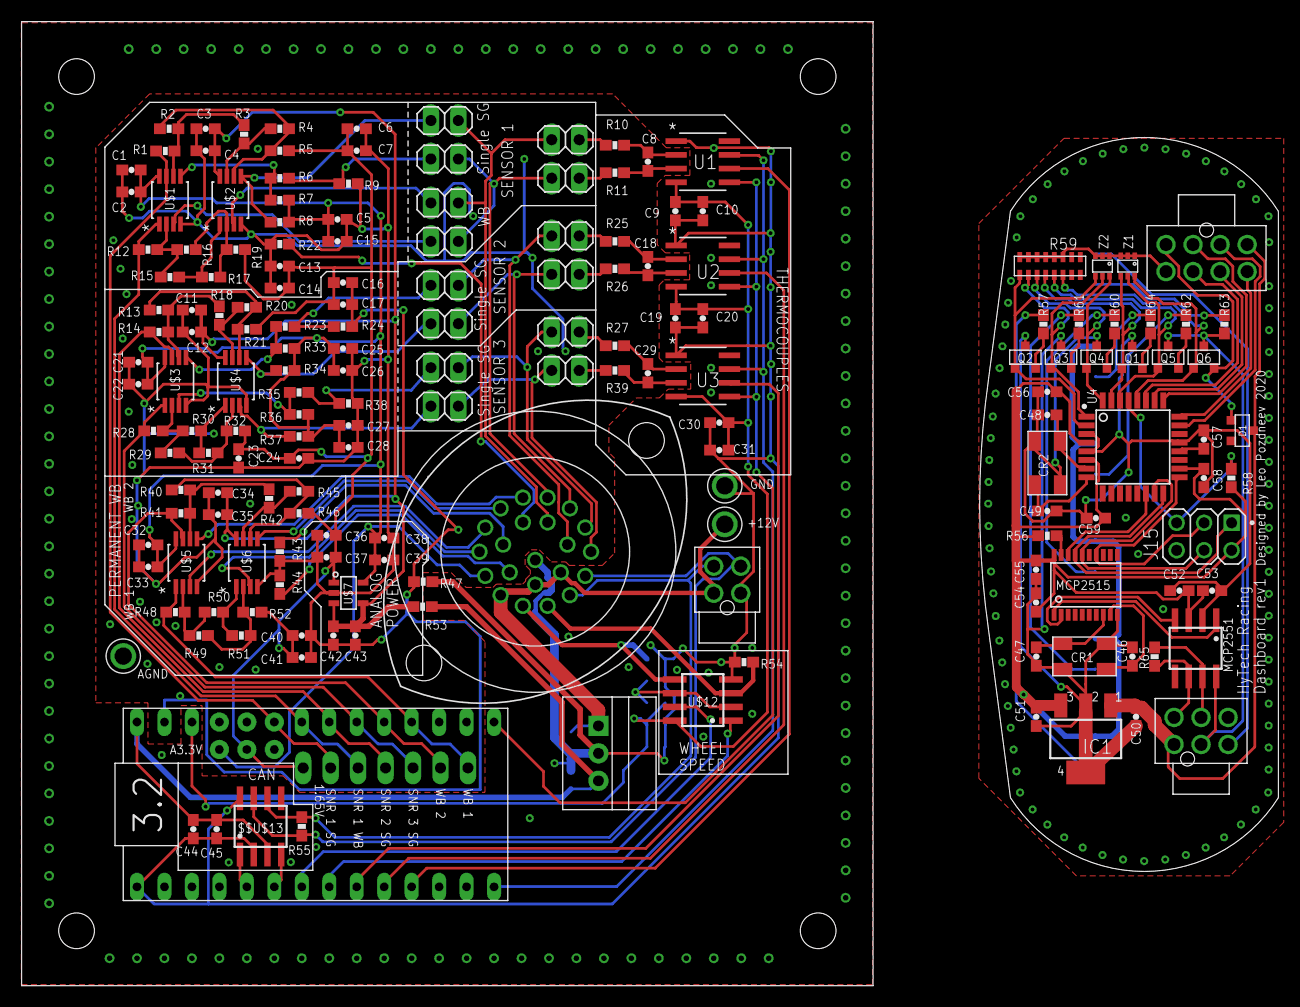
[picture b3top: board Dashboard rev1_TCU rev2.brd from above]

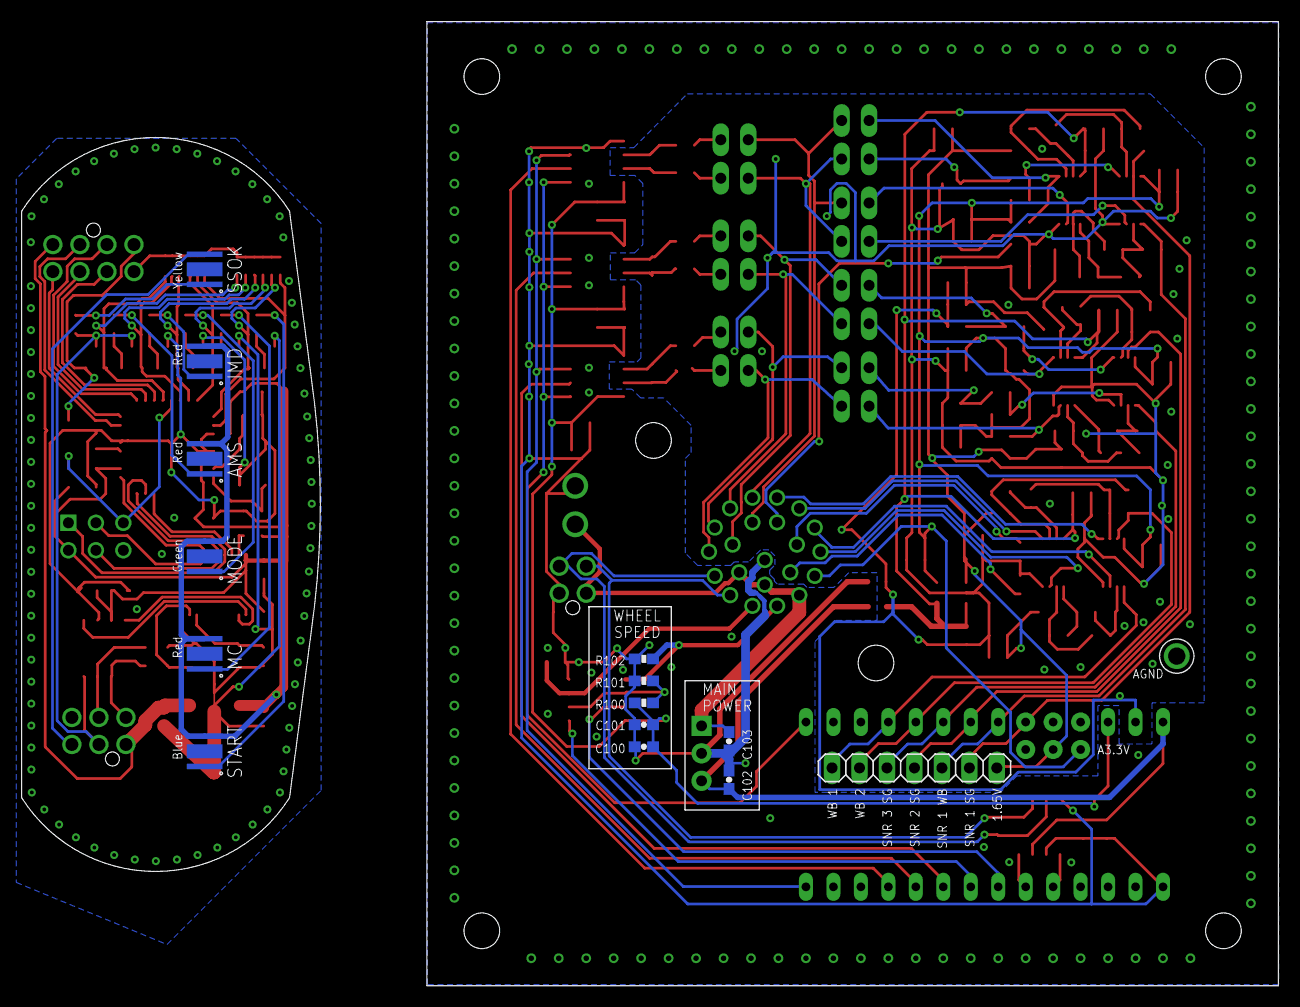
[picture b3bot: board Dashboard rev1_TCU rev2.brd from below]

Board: 2 copper layers, 116.2 x 89.2 mm, 189 parts (14 on the bottom side), 124 nets.

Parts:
$$U$11: TEST_POINT
$$U$13: MCP2551; SOIC-08
$$X2: CONNECTOR-8NANO-FIT_VERTICAL-8; NANO-FIT_VERTICAL-8
AMS: Red; CREE_XP-E2
C1, C3, C5, C6, C10, C11, C13, C16, C20, C22, C24, C26, C27, C31, C32, C34, C37, C38, C40, C43, C52, C54, C100: 1uF; 0603-CAP
C2, C4, C7, C12, C14, C15, C17, C21, C23, C25, C28, C33, C35, C36, C39, C41, C42, C57, C101: .1uF; 0603-CAP
C8, C18, C29: 10nF; 0603-CAP
C9, C19, C30, C51, C53, C55, C56, C58, C59: 0.1uF; 0603-CAP
C44: 1 uF; 0603-CAP
C45: .1 uF; 0603-CAP
C46, C47, C48, C49: 14pF; 0603-CAP
C50: 0.22uF; 0603-CAP
C102, C103: 10uF; 0603-CAP
CR1, CR2: 16MHz, 10pF; ABM3B
D1: DIODE_ZENER; SOT23
IC1: LM340S; SOT223
IMD: Red; CREE_XP-E2
J1, J2, J3, J4, J5, J6, J7, J8, J9, J10, J11, J12, J13, J14: JUMPER.1; 1X02
J15: AVR-ISP-HEADER; 2X03
MC: Red; CREE_XP-E2
MCP2515: MCP2515TSSOP; TSSOP-20
MCP2551: MCP2551; SOIC-08
MODE: Green; CREE_XP-E2
Q1, Q2, Q3, Q4, Q5, Q6: SOT23
R1, R5, R12, R14, R19, R21, R28, R32, R41, R46, R48, R52: 20k; 0603-RES
R2, R13: 86.6; 0603-RES
R3, R4, R15, R17, R18, R20, R30, R31, R42, R45, R50, R51: 5.1k; 0603-RES
R6, R7, R8, R23, R33, R34, R35, R36, R37, R65: 120; 0603-RES
R9, R22, R24, R38, R43, R44: 1.27k; 0603-RES
R10, R11, R25, R26, R27, R39, R47, R53: 0; 0603-RES
R16, R29, R40, R49: 177.7; 0603-RES
R54, R102: 150; 0603-RES
R55: 220; 0603-RES
R56, R58: 10k; 0603-RES
R57, R60, R61, R62, R63, R64: 0603-RES
R59: 10k; CAT16-*8
R100, R101: 1k; 0603-RES
REG: 5V; OKI-78SR
SSOK: Yellow; CREE_XP-E2
START: Blue; CREE_XP-E2
U1, U2, U3: MAX31855KASA+; 21-0041B_8
U4: ATMEGA328P-AU; QFP80P900X900X120-32N
U$1, U$2, U$3, U$4, U$5, U$6: LTC6081; MSOP-8_MS
U$7: REF2033; SOT-23-5
U$8: CONNECTOR-22; AUTOSPORT_12-35
U$9, U$10: TEST_POINT
U$12: MCP6002SOIC; SOIC-08
U$14: TEENSY_3.2_EXT_12ANALOG_AREF
U$100: M07; 1X07
X1: CONNECTOR-6NANO-FIT_VERTICAL-6; NANO-FIT_VERTICAL-6
X7: CONNECTOR-4NANO-FIT-VERTICAL-4; NANO-FIT_VERTICAL-4
Z1, Z2: MMBZ5245BTS-7-F; SOT363

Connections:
+1V65A: C6.1, C7.1, C13.1, C14.1, C16.1, C17.1, C23.1, C24.1, C36.1, C37.1, C40.1, C41.1, R5.2, R19.1, R21.2, R32.1, R46.2, R52.1, U$7.1, U$14.A10, U$100.1
+3V3: C9.1, C10.1, C19.1, C20.1, C30.1, C31.1, C100.1, C101.1, R100.2, U1.4, U2.4, U3.4, U$12.8, U$14.3.3V
+3V3A: C1.1, C2.1, C5.1, C15.1, C21.1, C22.1, C25.1, C26.1, C27.1, C28.1, C32.1, C33.1, C38.1, C39.1, R7.1, R8.2, R33.1, R34.2, R36.1, R37.2, U$1.8, U$3.8, U$5.8, U$7.5, U$8.P$10, U$14.AREF
+5V: $$U$13.3, C44.2, C45.2, C102.2, R53.1, REG.3, U$14.VIN
+5V1: AMS.P$1, C51.1, C52.1, C53.1, C54.1, C55.1, C56.1, C58.1, C59.1, IC1.3, IMD.P$1, J15.2, MC.P$1, MCP2515.20, MCP2551.3, MODE.P$1, R56.2, R58.2, START.P$1, U4.4, U4.6, U4.18
+5VA: C3.1, C4.1, C11.1, C12.1, C34.1, C35.1, C42.1, C43.1, R53.2, U$2.8, U$4.8, U$6.8, U$7.3, U$7.4
+12V: C103.2, REG.1, U$8.P$9, U$8.P$16, U$8.P$21, U$10.P$1, X7.P$1
+12V1: $$X2.P$1, C50.2, D1.3, IC1.1, X1.P$1
AGND: $$U$11.P$1, C1.2, C2.2, C3.2, C4.2, C5.2, C6.2, C7.2, C11.2, C12.2, C13.2, C14.2, C15.2, C16.2, C17.2, C21.2, C22.2, C23.2, C24.2, C25.2, C26.2, C27.2, C28.2, C32.2, C33.2, C34.2, C35.2, C36.2, C37.2, C38.2, C39.2, C40.2, C41.2, C42.2, C43.2, R9.1, R22.1, R24.1, R38.1, R43.1, R44.1, R47.2, U$1.4, U$2.4, U$3.4, U$4.4, U$5.4, U$6.4, U$7.2, U$14.AGND
BTN_EXTRA: $$X2.P$7, U4.27
BTN_MARK_READ: $$X2.P$2, U4.23
BTN_MC_CYCLE_READ: $$X2.P$3, U4.25
BTN_MODE_READ: $$X2.P$5, U4.24
BTN_START_READ: $$X2.P$6, U4.26
BUZZER_CTRL: Q6.1, R59.P$6, U4.28, Z1.P$4
BUZZER_OUT: $$X2.P$4, D1.1, Q6.2
CANH: $$U$13.7, R55.1, U$8.P$5, X7.P$4
CANH1: MCP2551.7, R65.1, X1.P$5
CANL: $$U$13.6, R55.2, U$8.P$6, X7.P$3
CANL1: MCP2551.6, R65.2, X1.P$4
CANRX: $$U$13.4, U$14.D4(CANRX)
CANTX: $$U$13.1, U$14.D3(CANTX)
CS: MCP2515.18, U4.14
CS1: U1.6, U$14.D9(RX2)
CS2: U2.6, U$14.D8(TX3)
CS3: U3.6, U$14.D7(RX3)
GND: $$U$13.2, $$U$13.8, C9.2, C10.2, C19.2, C20.2, C30.2, C31.2, C44.1, C45.1, C100.2, C101.2, C102.1, C103.1, R47.1, R54.2, R101.2, R102.1, REG.2, U1.1, U2.1, U3.1, U$8.P$20, U$9.P$1, U$12.4, U$14.GND, X7.P$2
GND1: $$X2.P$8, C46.2, C47.1, C48.1, C49.2, C50.1, C51.2, C52.2, C53.2, C54.2, C55.2, C56.2, C57.2, C58.2, C59.2, CR1.P$2, CR1.P$4, CR2.P$2, CR2.P$4, IC1.2, IC1.4, J15.6, MCP2515.10, MCP2551.2, MCP2551.8, Q1.3, Q2.3, Q3.3, Q4.3, Q5.3, Q6.3, R59.P$11, R59.P$12, R59.P$13, R59.P$14, R59.P$15, R59.P$16, R63.2, U4.3, U4.5, U4.21, X1.P$2, Z1.P$1, Z1.P$2, Z1.P$3, Z2.P$1, Z2.P$2, Z2.P$3
LED_AMS_CTRL: Q5.1, R59.P$5, U4.30, Z1.P$5
LED_IMD_CTRL: Q1.1, R59.P$4, U4.31, Z1.P$6
LED_MC_ERR_CTRL: Q3.1, R59.P$2, U4.1, Z2.P$5
LED_MODE_CTRL: Q4.1, R59.P$3, U4.32, Z2.P$4
LED_START_CTRL: Q2.1, R59.P$1, U4.2, Z2.P$6
MISO: U1.7, U2.7, U3.7, U$14.D12
MISO1: J15.1, MCP2515.17, U4.16
MOSI: J15.4, MCP2515.16, U4.15
unnamed: R50.2, R51.2, U$6.1
unnamed: C8.1, R10.2, U1.2
unnamed: R49.2, R51.1, R52.2, U$6.2
unnamed: R40.2, R45.2, R46.1, U$6.6
unnamed: R48.1, R49.1, R50.1, U$5.2
unnamed: C8.2, R11.2, U1.3
unnamed: MCP2515.19, R56.1
unnamed: R42.2, R45.1, U$6.7
unnamed: R40.1, R41.2, R42.1, U$5.6
unnamed: R16.2, R17.1, R19.2, U$2.2
unnamed: R2.2, R4.2, R5.1, U$2.6
unnamed: R15.2, R17.2, U$2.1
unnamed: R12.1, R15.1, R16.1, U$1.2
unnamed: R3.2, R4.1, U$2.7
unnamed: C18.1, R25.2, U2.2
unnamed: C18.2, R26.2, U2.3
unnamed: R29.2, R31.1, R32.2, U$4.2
unnamed: R13.2, R20.2, R21.1, U$4.6
unnamed: R30.2, R31.2, U$4.1
unnamed: C46.1, CR1.P$3, MCP2515.9
unnamed: R28.1, R29.1, R30.1, U$3.2
unnamed: R18.2, R20.1, U$4.7
unnamed: R13.1, R14.2, R18.1, U$3.6
unnamed: C47.2, CR1.P$1, MCP2515.8
unnamed: C29.1, R27.2, U3.2
unnamed: C29.2, R39.2, U3.3
unnamed: C48.2, CR2.P$1, U4.7
unnamed: C49.1, CR2.P$3, U4.8
unnamed: Q2.2, R57.2
unnamed: Q4.2, R60.2
unnamed: MODE.P$2, R60.1
unnamed: Q1.2, R64.2
unnamed: IMD.P$2, R64.1
unnamed: R63.1, SSOK.P$2
unnamed: AMS.P$2, R62.1
unnamed: Q5.2, R62.2
unnamed: Q3.2, R61.2
unnamed: MC.P$2, R61.1
unnamed: C57.1, U4.20
unnamed: R57.1, START.P$2
unnamed: R1.2, R2.1, R3.1, U$1.6
RESET: J15.5, R58.1, U4.29
RX: MCP2515.2, MCP2551.4
SCK: U1.5, U2.5, U3.5, U$14.D13
SCK1: J15.3, MCP2515.14, U4.17
SG1_GND*: R44.2, U$8.P$17
SG1_V+: U$6.3, U$8.P$11
SG1_V-: U$5.3, U$8.P$22
SG1_VOUT: R48.2, U$5.1, U$14.A2, U$100.7
SG2_GND*: R43.2, U$8.P$18
SG2_V+: U$6.5, U$8.P$12
SG2_V-: U$5.5, U$8.P$13
SG2_VOUT: R41.1, U$5.7, U$14.A3, U$100.6
SNR3_SG_GND*: J12.2, R35.1, R38.2
SRN1-1: J2.1, J5.1, J6.1, U$8.P$1
SRN1-2: J1.1, J3.1, J4.1, U$8.P$14
SRN1_SG_GND*: J2.2, R6.1, R9.2
SRN1_SG_V+: J1.2, R8.1, U$2.5
SRN1_SG_V-: R6.2, R7.2, U$1.5
SRN1_SG_VOUT: R1.1, U$1.7, U$14.A7, U$100.2
SRN1_T+: J5.2, R11.1
SRN1_T-: J4.2, R10.1
SRN1_WB_GND*: R22.2, U$8.P$19
SRN1_WB_V+: J3.2, U$2.3
SRN1_WB_V-: J6.2, U$1.3
SRN1_WB_VOUT: R12.2, U$1.1, U$14.A6, U$100.3
SRN2-1: J8.1, J10.1, U$8.P$2
SRN2-2: J7.1, J9.1, U$8.P$15
SRN2_SG_GND*: J7.2, R23.1, R24.2
SRN2_SG_V+: J8.2, R34.1, U$4.5
SRN2_SG_V-: R23.2, R33.2, U$3.5
SRN2_SG_VOUT: R14.1, U$3.7, U$14.A5, U$100.4
SRN2_T+: J10.2, R26.1
SRN2_T-: J9.2, R25.1
SRN3-1: J13.1, J14.1, U$8.P$4
SRN3-2: J11.1, J12.1, U$8.P$3
SRN3_SG_V+: J13.2, R37.1, U$4.3
SRN3_SG_V-: R35.2, R36.2, U$3.3
SRN3_SG_VOUT: R28.2, U$3.1, U$14.A4, U$100.5
SRN3_T+: J14.2, R39.1
SRN3_T-: J11.2, R27.1
SSOK: SSOK.P$1, X1.P$3
TX: MCP2515.1, MCP2551.1
V_DIV: R100.1, R101.1, U$12.2, U$12.6
WS1: U$12.1, U$14.D6
WS1_OUT: R54.1, U$8.P$7, U$12.3
WS2: U$12.7, U$14.D5
WS2_OUT: R102.2, U$8.P$8, U$12.5
